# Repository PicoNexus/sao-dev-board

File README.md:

# SAO Development Board

This is a development and debugging platform for SAOs, standing in for a badge, and based on the Raspberry Pi Pico family of microcontroller boards.

In addition to the Pico, there is a small OLED screen, a few LEDs, reset button and a 5-way navigation switch, to support the badge features.

There is also a set of jumpers and 2 4mm bananaplugs, meant for different ways to power the board and SAO, or for measuring current usage of the SAO using an external tool (eg multimeter or power profiler)

## Designed in KiCad v8.99 (nightly)

To open the project, you will need to install a recent nightly build (og v9 or newer when released), KiCad v8 or earlier won't open this design directly.

## License

The hardware design of the `main` branch of this repository is released under the following license:

* the "Creative Commons Attribution-ShareAlike 4.0 International License"
  (CC BY-SA 4.0) full text of this license is included in the LICENSE file
  and a copy can also be found at
  [http://creativecommons.org/licenses/by-sa/4.0/](http://creativecommons.org/licenses/by-sa/4.0/)

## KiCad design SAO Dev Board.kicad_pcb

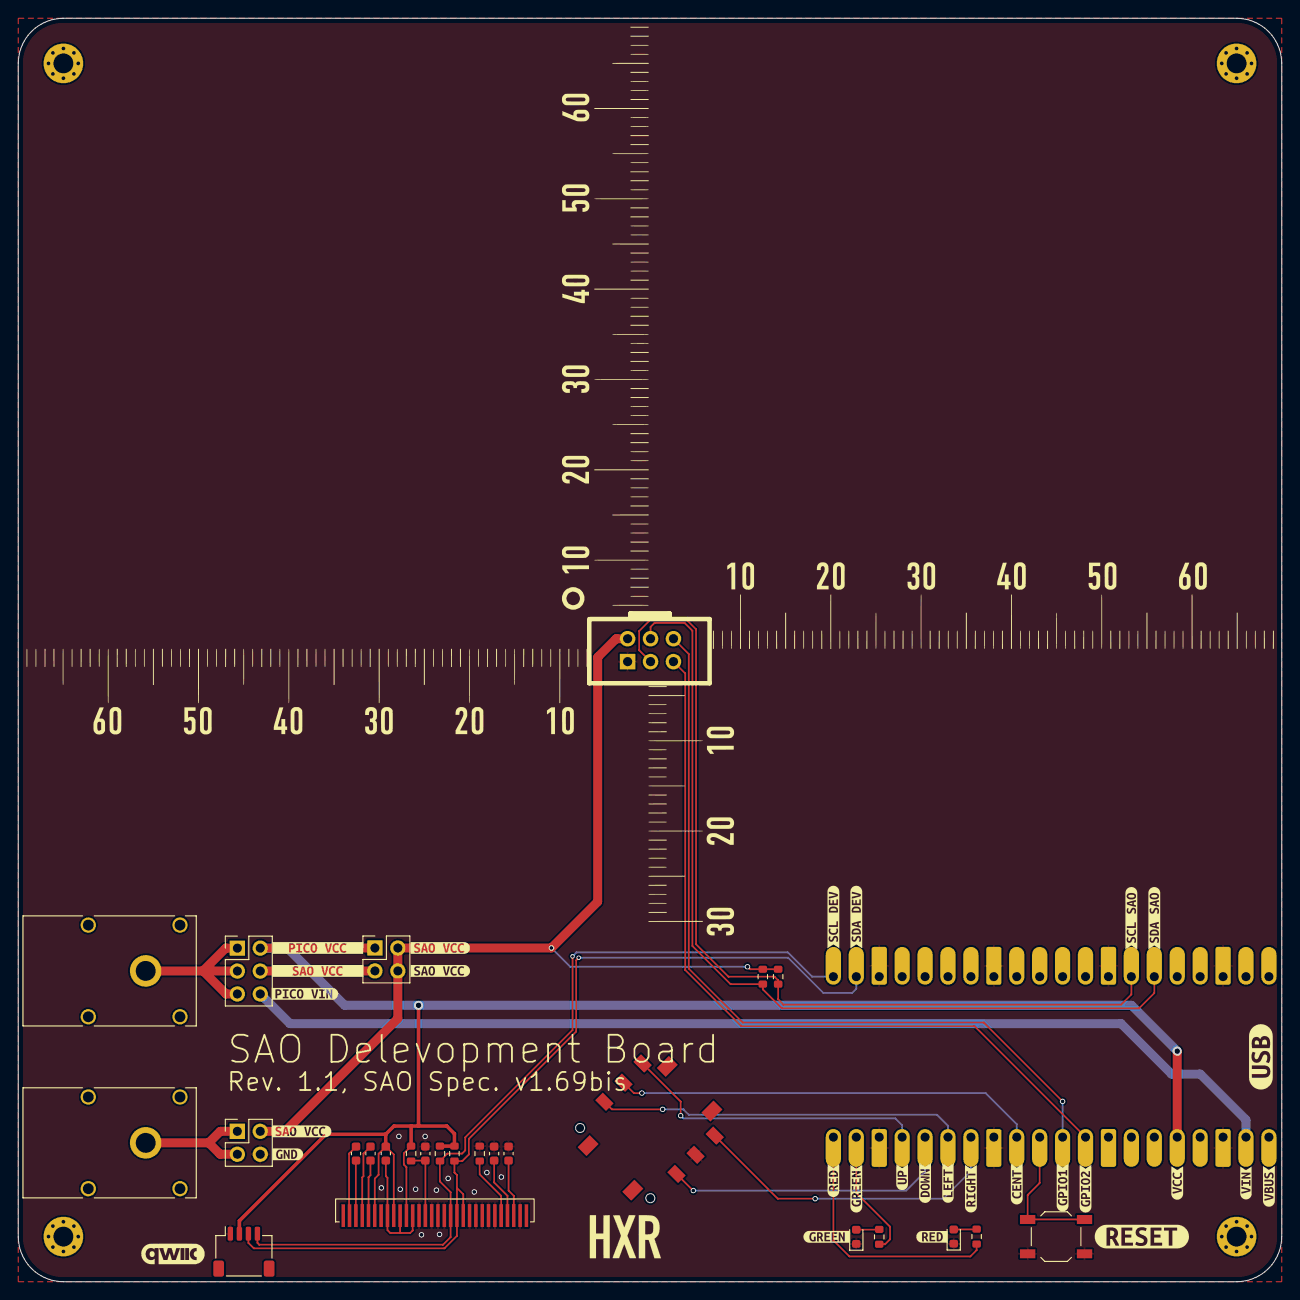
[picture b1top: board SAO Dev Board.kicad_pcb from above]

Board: 2 copper layers, 140.0 x 140.0 mm, 55 parts (0 on the bottom side), 32 nets.

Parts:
C1, C2, C3: 1uF; C_0603_1608Metric
C4: 2.2uF; C_0603_1608Metric
C5: 100nF; C_0603_1608Metric
C6: 10uF; C_0603_1608Metric
D1: LED_GREEN; LED_0603_1608Metric
D2: LED_RED; LED_0603_1608Metric
J1: 4mm Banana, red; Banana_Cliff_FCR7350R_S16N-PC_Horizontal
J2: 4mm Banana, black; Banana_Cliff_FCR7350B_S16N-PC_Horizontal
J3: Conn_02x03_Odd_Even; PinHeader_2x03_P2.54mm_Vertical
J4, J5: Conn_02x02_Odd_Even; PinHeader_2x02_P2.54mm_Vertical
J6: LCSC C145956; JST_SH_SM04B-SRSS-TB_1x04-1MP_P1.00mm_Horizontal
J7, J8: Conn_01x20_Socket; PinSocket_1x20_P2.54mm_Vertical
OLEDM1: SSD1306; IROP055-SSD1306Z-PADS-ONLY
R1, R2: 3.3k; R_0603_1608Metric
R3, R4: 1k; R_0603_1608Metric
R5, R6, R7: 10K; R_0603_1608Metric
R8: 330K; R_0603_1608Metric
SW1: 5-Way_Switch; TE-2425755-1
SW2: TS5220A; SW_SPST_TL3342
X1: sao_v169bis; Badgelife-SAOv169-BADGE-2x3
kibuzzard-66F97EBB: G***; kibuzzard-66F97EBB
kibuzzard-66F97F8D: G***; kibuzzard-66F97F8D
kibuzzard-66F97F28: G***; kibuzzard-66F97F28
kibuzzard-66F97F40: G***; kibuzzard-66F97F40
kibuzzard-66F97F94: G***; kibuzzard-66F97F94
kibuzzard-66F97FA0: G***; kibuzzard-66F97FA0
kibuzzard-66F97FBA: G***; kibuzzard-66F97FBA
kibuzzard-66F97FD1: G***; kibuzzard-66F97FD1
kibuzzard-66F97FDE: G***; kibuzzard-66F97FDE
kibuzzard-66F980B1: G***; kibuzzard-66F980B1
kibuzzard-66F981A0: G***; kibuzzard-66F981A0
kibuzzard-66F982A7, kibuzzard-66F982A7#2, kibuzzard-66F982A7#3: G***; kibuzzard-66F982A7
kibuzzard-66F982C8: G***; kibuzzard-66F982C8
kibuzzard-66F982DE: G***; kibuzzard-66F982DE
kibuzzard-66F983EF: G***; kibuzzard-66F983EF
kibuzzard-66F984DA: G***; kibuzzard-66F984DA
kibuzzard-66F9816D: G***; kibuzzard-66F9816D
kibuzzard-66F9817D: G***; kibuzzard-66F9817D
kibuzzard-66F98024: G***; kibuzzard-66F98024
kibuzzard-66F98092: G***; kibuzzard-66F98092
kibuzzard-66F98199: G***; kibuzzard-66F98199
kibuzzard-66F98571: G***; kibuzzard-66F98571
kibuzzard-670E5162: G***; kibuzzard-670E5162
kibuzzard-670E5178: G***; kibuzzard-670E5178
kibuzzard-670E5189: G***; kibuzzard-670E5189

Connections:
/RPi Pico X/RUN: J8.10, SW2.2 (B)
BTN_CENTER: J8.9, SW1.2 (Center)
BTN_DOWN: J8.5, SW1.6 (Down)
BTN_LEFT: J8.6, SW1.3 (Left)
BTN_RIGHT: J8.7, SW1.4 (Right)
BTN_UP: J8.4, SW1.1 (Up)
GND: C4.2, C5.1, C6.2, D1.1 (K), D2.1 (K), J4.4, J6.1, J7.3, J7.8, J7.13, J7.18, J8.3, J8.8, J8.18, OLEDM1.13 (CS#), OLEDM1.15 (C/D#), OLEDM1.16 (R/W#), OLEDM1.17 (E_RD#), OLEDM1.21 (DB3), OLEDM1.22 (DB4), OLEDM1.23 (DB5), OLEDM1.24 (DB6), OLEDM1.25 (DB7), OLEDM1.29 (VLSS), R8.2, SW1.5 (Common), SW2.1 (A), X1.2 (GND)
I2C0_SCL: J7.7, R2.2, X1.4 (SCL)
I2C0_SDA: J7.6, R1.2, X1.3 (SDA)
I2C1_SCL: J6.4, J7.20, OLEDM1.18 (DB0), R7.2
I2C1_SDA: J6.3, J7.19, OLEDM1.19 (DB1), OLEDM1.20 (DB2), R6.2
LED_GREEN: J8.2, R3.1
LED_RED: J8.1, R4.1
unnamed: D1.2 (A), R3.2
unnamed: D2.2 (A), R4.2
unnamed: J1.1, J3.1, J3.3, J3.5
unnamed: J2.1, J4.1, J4.3
unnamed: J3.4, J5.3
unnamed: C3.2, OLEDM1.8 (VSS), OLEDM1.10 (BS0), OLEDM1.12 (BS2)
unnamed: C2.2, OLEDM1.5 (CAP1N)
unnamed: C2.1, OLEDM1.4 (CAP1P)
unnamed: C1.2, OLEDM1.3 (CAP2N)
unnamed: C1.1, OLEDM1.2 (CAP2P)
unnamed: OLEDM1.26 (IREF), R8.1
unnamed: C5.2, OLEDM1.14 (RES#), R5.2
unnamed: C4.1, OLEDM1.28 (VCC)
unnamed: C6.1, OLEDM1.27 (VCOMH)
PICO_VIN: J3.6, J8.19
SAO_GPIO1: J8.11, X1.5 (GPIO1)
SAO_GPIO2: J8.12, X1.6 (GPIO2)
SAO_VCC: J4.2, J5.2, J5.4, R1.1, R2.1, X1.1 (VCC)
VCC: C3.1, J3.2, J5.1, J6.2, J8.16, OLEDM1.6 (VBAT), OLEDM1.9 (VDD), OLEDM1.11 (BS1), R5.1, R6.1, R7.1

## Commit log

2024-11-02 Fixed rotated connector
2024-11-02 Added 3D printed parts
2024-11-02 Added readme, license and schematics as PDF
2024-11-02 Fixed typo
2025-06-10 Added photos
